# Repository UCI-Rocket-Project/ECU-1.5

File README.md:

# UCIRP Engine Control Unit (ECU)
Hardware design files for ECU v1.5 "Orion"

Minimal, stable ECU for VTF and launch.

## Used Packages
* Teensy 4.1 [symbol](https://github.com/XenGi/teensy_library) and [footprint](https://github.com/XenGi/teensy.pretty). Related files and license is located under `/teensylib`.

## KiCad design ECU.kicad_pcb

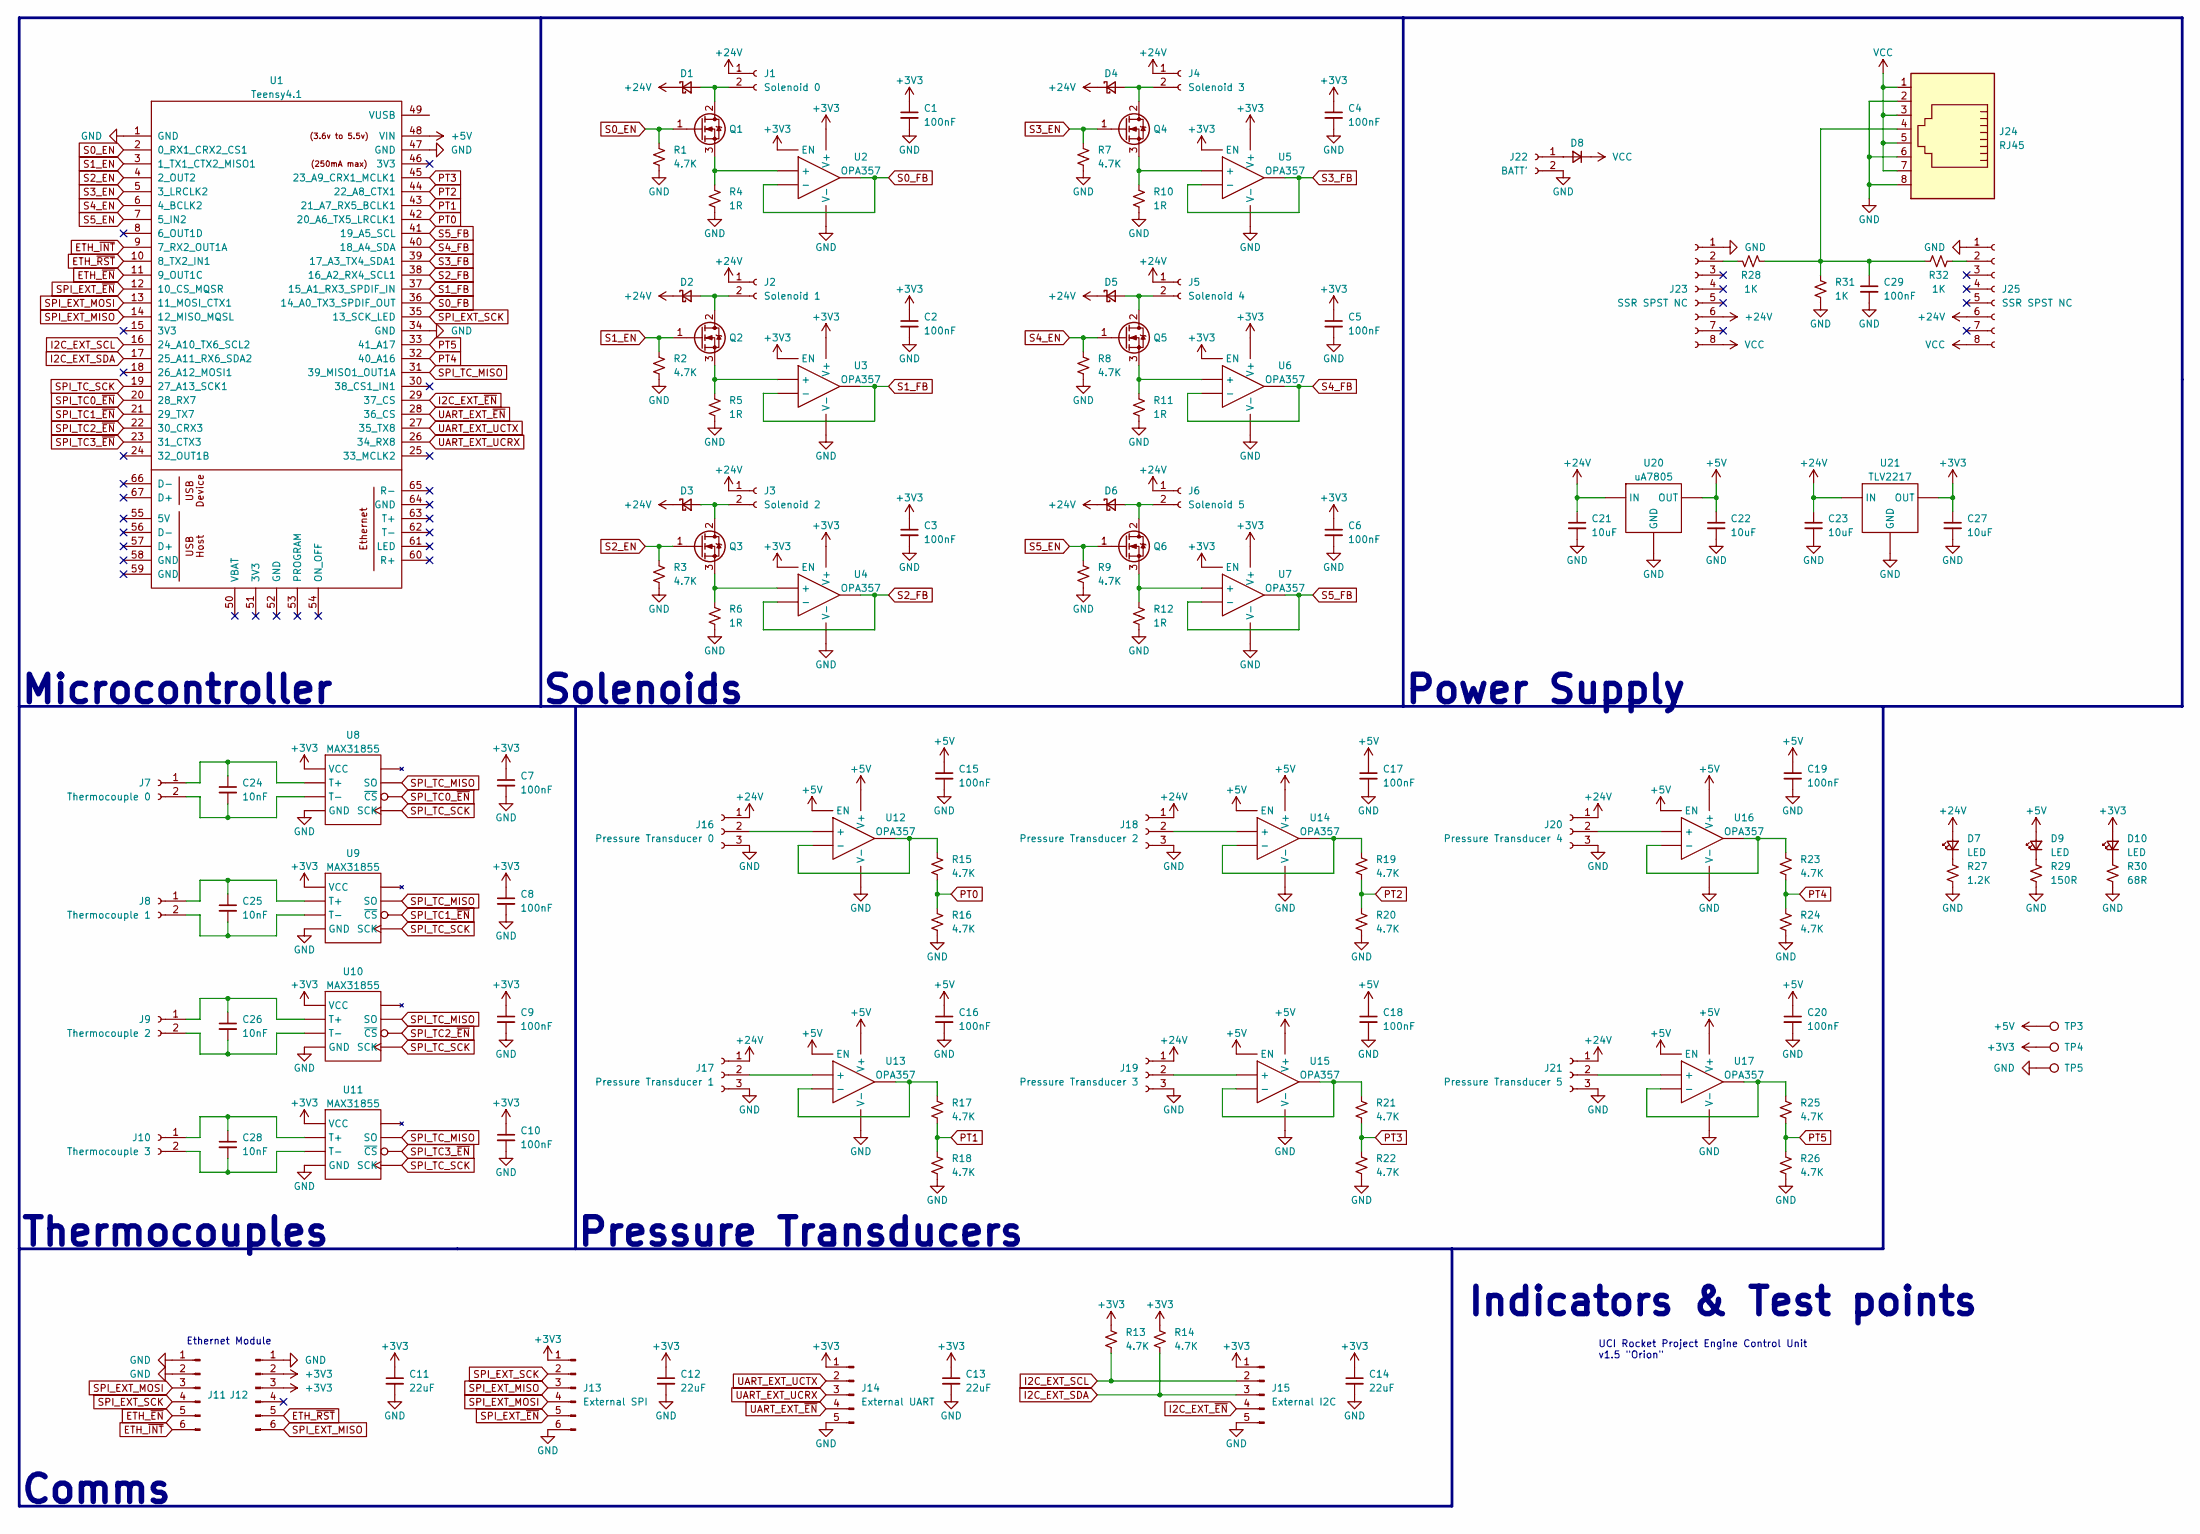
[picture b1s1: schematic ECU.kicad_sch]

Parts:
C1, C2, C3, C4, C5, C6, C7, C8, C9, C10, C15, C16, C17, C18, C19, C20, C29: 100nF; C_0603_1608Metric; Part # Generic 100nF 0603 MLCC
C11, C12, C13, C14: 22uF; C_0805_2012Metric; Part # Generic 22uF 0805 MLCC
C21, C22, C23, C27: 10uF; C_1206_3216Metric; Part # Generic 10uF 1206 MLCC
C24, C25, C26, C28: 10nF; C_0603_1608Metric; Part # Generic 10nF 0603 MLCC
D1, D2, D3, D4, D5, D6: D_SOD-523; Part # SDM20U40Q-7
D7, D9, D10: LED; D_0603_1608Metric; Part # Generic Red 0603 LED
D8: D_SMA
J1: Solenoid 0; TerminalBlock_bornier-2_P5.08mm; Part # Generic 2x5.08 Screw Terminal
J2: Solenoid 1; TerminalBlock_bornier-2_P5.08mm; Part # Generic 2x5.08 Screw Terminal
J3: Solenoid 2; TerminalBlock_bornier-2_P5.08mm; Part # Generic 2x5.08 Screw Terminal
J4: Solenoid 3; TerminalBlock_bornier-2_P5.08mm; Part # Generic 2x5.08 Screw Terminal
J5: Solenoid 4; TerminalBlock_bornier-2_P5.08mm; Part # Generic 2x5.08 Screw Terminal
J6: Solenoid 5; TerminalBlock_bornier-2_P5.08mm; Part # Generic 2x5.08 Screw Terminal
J7: Thermocouple 0; TerminalBlock_bornier-2_P5.08mm; Part # Generic 2x5.08 Screw Terminal
J8: Thermocouple 1; TerminalBlock_bornier-2_P5.08mm; Part # Generic 2x5.08 Screw Terminal
J9: Thermocouple 2; TerminalBlock_bornier-2_P5.08mm; Part # Generic 2x5.08 Screw Terminal
J10: Thermocouple 3; TerminalBlock_bornier-2_P5.08mm; Part # Generic 2x5.08 Screw Terminal
J11, J12: PinHeader_1x06_P2.54mm_Vertical; Part # Generic 6x2.54 Pin Header
J13: External SPI; PinHeader_1x06_P2.54mm_Vertical; Part # Generic 6x2.54 Pin Header
J14: External UART; PinHeader_1x05_P2.54mm_Vertical; Part # Generic 5x2.54 Pin Header
J15: External I2C; PinHeader_1x05_P2.54mm_Vertical; Part # Generic 5x2.54 Pin Header
J16: Pressure Transducer 0; TerminalBlock_bornier-3_P5.08mm; Part # Generic 3x5.08 Screw Terminal
J17: Pressure Transducer 1; TerminalBlock_bornier-3_P5.08mm; Part # Generic 3x5.08 Screw Terminal
J18: Pressure Transducer 2; TerminalBlock_bornier-3_P5.08mm; Part # Generic 3x5.08 Screw Terminal
J19: Pressure Transducer 3; TerminalBlock_bornier-3_P5.08mm; Part # Generic 3x5.08 Screw Terminal
J20: Pressure Transducer 4; TerminalBlock_bornier-3_P5.08mm; Part # Generic 3x5.08 Screw Terminal
J21: Pressure Transducer 5; TerminalBlock_bornier-3_P5.08mm; Part # Generic 3x5.08 Screw Terminal
J22: BATT'; TerminalBlock_bornier-2_P5.08mm; Part # Generic 2x5.08 Screw Terminal
J23, J25: SSR SPST NC; SIP-8_19x3mm_P2.54mm
J24: RJ45; RJ45_Amphenol_54602-x08_Horizontal
Q1, Q2, Q3, Q4, Q5, Q6: TO-220-3_Vertical; Part # CSD18542KCS
R1, R2, R3, R7, R8, R9, R13, R14, R15, R16, R17, R18, R19, R20, R21, R22, R23, R24, R25, R26: 4.7K; R_0603_1608Metric; Part # Generic 4.7K 0603 Resistor
R4, R5, R6, R10, R11, R12: 1R; R_0603_1608Metric; Part # Generic 1R 1W 0603 Resistor
R27: 1.2K; R_0603_1608Metric; Part # Generic 1.2K 0603 Resistor
R28, R31, R32: 1K; R_2512_6332Metric
R29: 150R; R_0603_1608Metric; Part # Generic 150R 0603 Resistor
R30: 68R; R_0603_1608Metric; Part # Generic 68R 0603 Resistor
TP3, TP4, TP5: TestPoint_Pad_D4.0mm
U1: Teensy4.1; Teensy41
U2, U3, U4, U5, U6, U7, U12, U13, U14, U15, U16, U17: OPA357; SOT-23-6; Part # OPA357AIDBVT
U8, U9, U10, U11: MAX31855; SOIC-8_3.9x4.9mm_P1.27mm; Part # MAX31855KASA+T
U20: uA7805; TO-220-3_Vertical; Part # UA7805CKCT
U21: TLV2217; TO-220-3_Vertical; Part # TLV2217-33KCSE3

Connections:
+3V3: C1.1, C2.1, C3.1, C4.1, C5.1, C6.1, C7.1, C8.1, C9.1, C10.1, C11.1, C12.1, C13.1, C14.1, C27.1, D10.2 (A), J12.2, J12.3, J13.1, J14.1, J15.1, R13.1, R14.1, TP4.1, U2.5 (EN), U2.6 (V+), U3.5 (EN), U3.6 (V+), U4.5 (EN), U4.6 (V+), U5.5 (EN), U5.6 (V+), U6.5 (EN), U6.6 (V+), U7.5 (EN), U7.6 (V+), U8.4 (VCC), U9.4 (VCC), U10.4 (VCC), U11.4 (VCC), U21.3 (OUT)
+5V: C15.1, C16.1, C17.1, C18.1, C19.1, C20.1, C22.1, D9.2 (A), TP3.1, U1.48 (VIN), U12.5 (EN), U12.6 (V+), U13.5 (EN), U13.6 (V+), U14.5 (EN), U14.6 (V+), U15.5 (EN), U15.6 (V+), U16.5 (EN), U16.6 (V+), U17.5 (EN), U17.6 (V+), U20.3 (OUT)
+24V: C21.1, C23.1, D1.1 (K), D2.1 (K), D3.1 (K), D4.1 (K), D5.1 (K), D6.1 (K), D7.2 (A), J1.1, J2.1, J3.1, J4.1, J5.1, J6.1, J16.1, J17.1, J18.1, J19.1, J20.1, J21.1, J23.6, J25.6, U20.1 (IN), U21.1 (IN)
ETH_~EN: J11.5, U1.11 (9_OUT1C)
ETH_~INT: J11.6, U1.9 (7_RX2_OUT1A)
ETH_~RST: J12.5, U1.10 (8_TX2_IN1)
GND: C1.2, C2.2, C3.2, C4.2, C5.2, C6.2, C7.2, C8.2, C9.2, C10.2, C11.2, C12.2, C13.2, C14.2, C15.2, C16.2, C17.2, C18.2, C19.2, C20.2, C21.2, C22.2, C23.2, C27.2, C29.2, J11.1, J11.2, J12.1, J13.6, J14.5, J15.5, J16.3, J17.3, J18.3, J19.3, J20.3, J21.3, J22.2, J23.1, J24.2, J24.6, J24.8, J25.1, R1.2, R2.2, R3.2, R4.2, R5.2, R6.2, R7.2, R8.2, R9.2, R10.2, R11.2, R12.2, R16.2, R18.2, R20.2, R22.2, R24.2, R26.2, R27.2, R29.2, R30.2, R31.2, TP5.1, U1.1 (GND), U1.34 (GND), U1.47 (GND), U2.2 (V-), U3.2 (V-), U4.2 (V-), U5.2 (V-), U6.2 (V-), U7.2 (V-), U8.1 (GND), U9.1 (GND), U10.1 (GND), U11.1 (GND), U12.2 (V-), U13.2 (V-), U14.2 (V-), U15.2 (V-), U16.2 (V-), U17.2 (V-), U20.2 (GND), U21.2 (GND)
I2C_EXT_SCL: J15.2, R13.2, U1.16 (24_A10_TX6_SCL2)
I2C_EXT_SDA: J15.3, R14.2, U1.17 (25_A11_RX6_SDA2)
I2C_EXT_~EN: J15.4, U1.29 (37_CS)
unnamed: C24.1, J7.1, U8.3 (T+)
unnamed: C24.2, J7.2, U8.2 (T-)
unnamed: C25.1, J8.1, U9.3 (T+)
unnamed: C25.2, J8.2, U9.2 (T-)
unnamed: C26.1, J9.1, U10.3 (T+)
unnamed: C26.2, J9.2, U10.2 (T-)
unnamed: C28.1, J10.1, U11.3 (T+)
unnamed: C28.2, J10.2, U11.2 (T-)
unnamed: C29.1, J24.4, R28.1, R31.1, R32.1
unnamed: D1.2 (A), J1.2, Q1.2 (D)
unnamed: D2.2 (A), J2.2, Q2.2 (D)
unnamed: D3.2 (A), J3.2, Q3.2 (D)
unnamed: D4.2 (A), J4.2, Q4.2 (D)
unnamed: D5.2 (A), J5.2, Q5.2 (D)
unnamed: D6.2 (A), J6.2, Q6.2 (D)
unnamed: D7.1 (K), R27.1
unnamed: D9.1 (K), R29.1
unnamed: D10.1 (K), R30.1
unnamed: J16.2, U12.3 (+)
unnamed: J17.2, U13.3 (+)
unnamed: J18.2, U14.3 (+)
unnamed: J19.2, U15.3 (+)
unnamed: J20.2, U16.3 (+)
unnamed: J21.2, U17.3 (+)
unnamed: D8.2 (A), J22.1
unnamed: J23.2, R28.2
unnamed: J25.2, R32.2
unnamed: Q1.3 (S), R4.1, U2.3 (+)
unnamed: Q2.3 (S), R5.1, U3.3 (+)
unnamed: Q3.3 (S), R6.1, U4.3 (+)
unnamed: Q4.3 (S), R10.1, U5.3 (+)
unnamed: Q5.3 (S), R11.1, U6.3 (+)
unnamed: Q6.3 (S), R12.1, U7.3 (+)
unnamed: R15.1, U12.1, U12.4 (-)
unnamed: R17.1, U13.1, U13.4 (-)
unnamed: R19.1, U14.1, U14.4 (-)
unnamed: R21.1, U15.1, U15.4 (-)
unnamed: R23.1, U16.1, U16.4 (-)
unnamed: R25.1, U17.1, U17.4 (-)
PT0: R15.2, R16.1, U1.42 (20_A6_TX5_LRCLK1)
PT1: R17.2, R18.1, U1.43 (21_A7_RX5_BCLK1)
PT2: R19.2, R20.1, U1.44 (22_A8_CTX1)
PT3: R21.2, R22.1, U1.45 (23_A9_CRX1_MCLK1)
PT4: R23.2, R24.1, U1.32 (40_A16)
PT5: R25.2, R26.1, U1.33 (41_A17)
S0_EN: Q1.1 (G), R1.1, U1.2 (0_RX1_CRX2_CS1)
S0_FB: U1.36 (14_A0_TX3_SPDIF_OUT), U2.1, U2.4 (-)
S1_EN: Q2.1 (G), R2.1, U1.3 (1_TX1_CTX2_MISO1)
S1_FB: U1.37 (15_A1_RX3_SPDIF_IN), U3.1, U3.4 (-)
S2_EN: Q3.1 (G), R3.1, U1.4 (2_OUT2)
S2_FB: U1.38 (16_A2_RX4_SCL1), U4.1, U4.4 (-)
S3_EN: Q4.1 (G), R7.1, U1.5 (3_LRCLK2)
S3_FB: U1.39 (17_A3_TX4_SDA1), U5.1, U5.4 (-)
S4_EN: Q5.1 (G), R8.1, U1.6 (4_BCLK2)
S4_FB: U1.40 (18_A4_SDA), U6.1, U6.4 (-)
S5_EN: Q6.1 (G), R9.1, U1.7 (5_IN2)
S5_FB: U1.41 (19_A5_SCL), U7.1, U7.4 (-)
SPI_EXT_MISO: J12.6, J13.3, U1.14 (12_MISO_MQSL)
SPI_EXT_MOSI: J11.3, J13.4, U1.13 (11_MOSI_CTX1)
SPI_EXT_SCK: J11.4, J13.2, U1.35 (13_SCK_LED)
SPI_EXT_~EN: J13.5, U1.12 (10_CS_MQSR)
SPI_TC0_~EN: U1.20 (28_RX7), U8.6 (~CS)
SPI_TC1_~EN: U1.21 (29_TX7), U9.6 (~CS)
SPI_TC2_~EN: U1.22 (30_CRX3), U10.6 (~CS)
SPI_TC3_~EN: U1.23 (31_CTX3), U11.6 (~CS)
SPI_TC_MISO: U1.31 (39_MISO1_OUT1A), U8.7 (SO), U9.7 (SO), U10.7 (SO), U11.7 (SO)
SPI_TC_SCK: U1.19 (27_A13_SCK1), U8.5 (SCK), U9.5 (SCK), U10.5 (SCK), U11.5 (SCK)
UART_EXT_UCRX: J14.3, U1.26 (34_RX8)
UART_EXT_UCTX: J14.2, U1.27 (35_TX8)
UART_EXT_~EN: J14.4, U1.28 (36_CS)
VCC: D8.1 (K), J23.8, J24.1, J24.3, J24.5, J24.7, J25.8

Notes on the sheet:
Microcontroller
Pressure Transducers
Solenoids
Thermocouples
UCI Rocket Project Engine Control Unit v1.5 "Orion"
Ethernet Module
Indicators & Test points
Comms
Power Supply

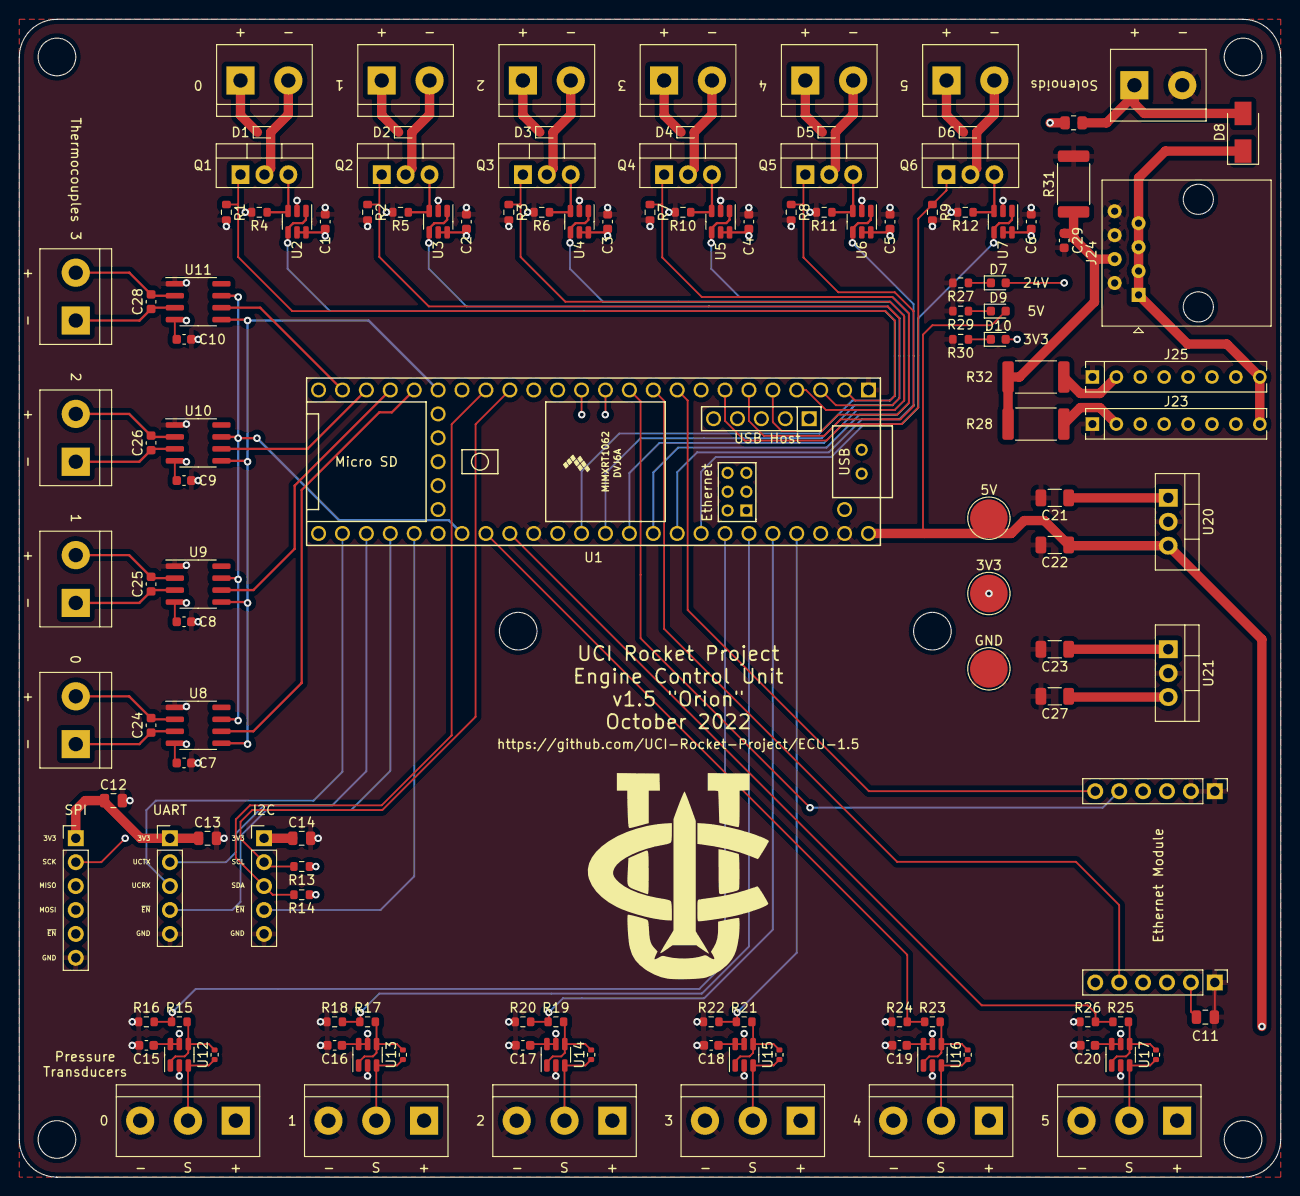
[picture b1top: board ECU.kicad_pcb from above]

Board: 4 copper layers, 134.0 x 123.0 mm, 124 parts (0 on the bottom side), 81 nets.

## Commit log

2022-10-19 Add teensy symbol and footprint
2022-10-20 Add ucontroller & solenoid switching design
2022-10-20 Add thermocouple design
2022-10-21 Add ethernet & external serial comms ports
2022-10-21 Reuse ethernet SPI bus for external devices
2022-10-21 Add I2C bus pullups
2022-10-22 Add pressure transducer design
2022-10-22 Add power supply, indicators, & test points
2022-10-22 Add PCB layout
2022-10-22 Correct resistor part numbers
2022-10-23 Add logo to silkscreen
2022-10-23 Add silkscreen labels for screw terminals
2023-04-17 Redesign power supply
2023-04-17 Add filter caps to TC input
2023-04-17 Integrate power switching & cutoff system
2023-04-17 Add bypass path for PT frontend
2023-04-17 Add bypass path for cutoff system
